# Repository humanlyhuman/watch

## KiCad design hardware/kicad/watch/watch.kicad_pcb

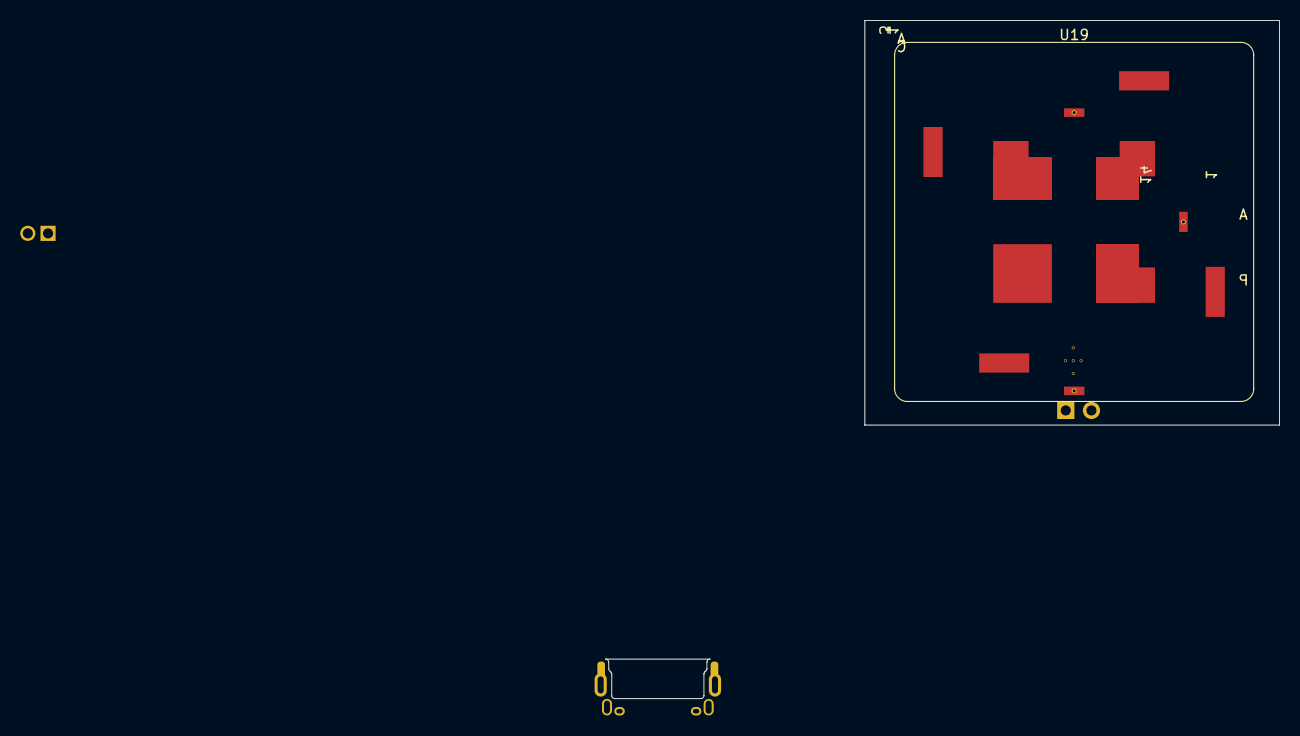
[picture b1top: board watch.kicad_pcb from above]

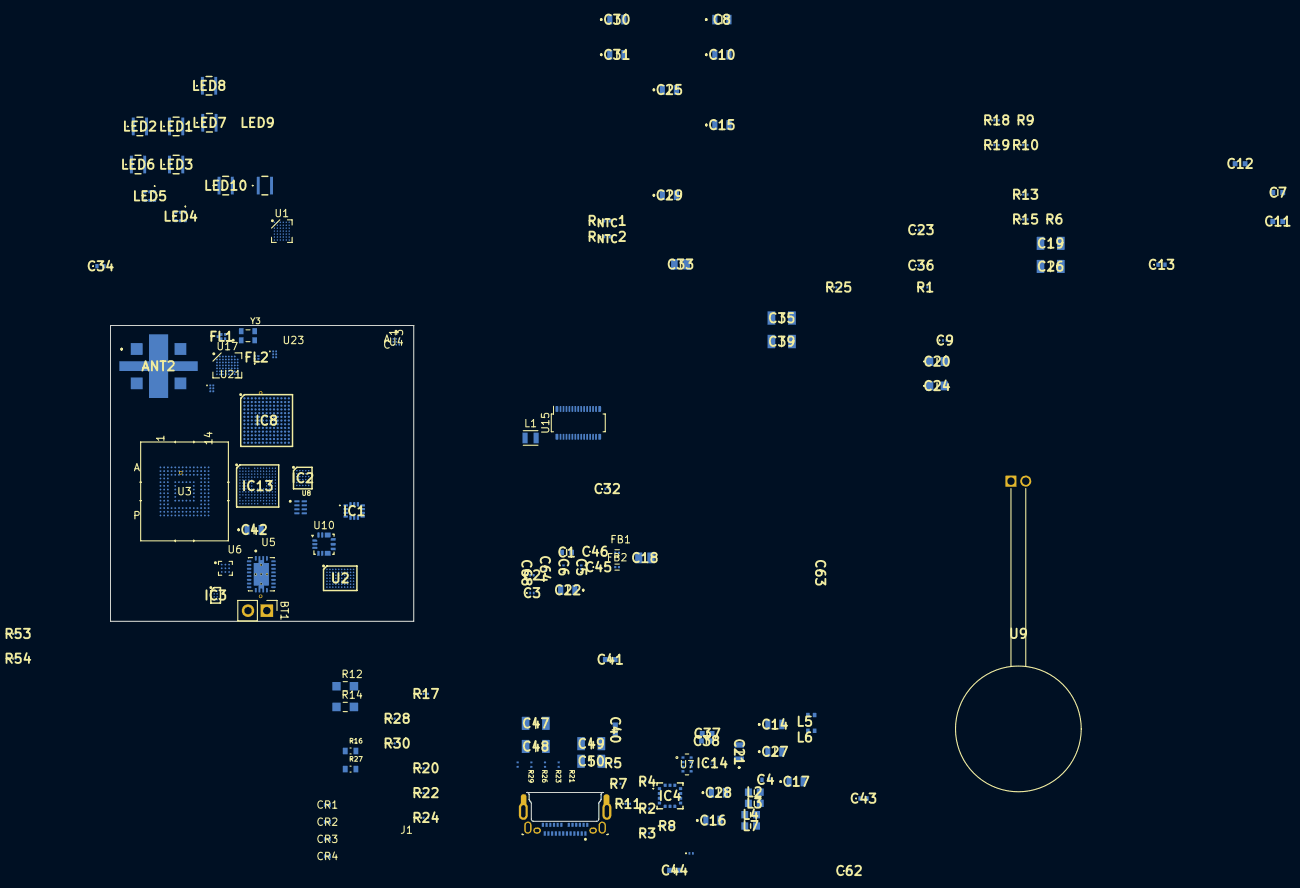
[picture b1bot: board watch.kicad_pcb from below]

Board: 8 copper layers, 139 parts (138 on the bottom side), 133 nets, no tracks yet.

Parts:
ANT2: HC125A
BT1: DTP793435-1S1P-1300mAh-3.85V; PinHeader_1x02_P2.54mm_Vertical
C1, C7, C11, C12, C44: 2.2uF; GRM18x
C2, C3, C5, C6, C9, C32, C36, C45, C46, C62, C63, C64, C68: 100nF; GRM033D70J224ME01D
C4, C13, C34, C43: 1uF; GRM155R61H334ME01D
C8, C14, C16, C17, C21, C22, C27, C28: 22uF; GRM21BR60J226ME39L
C10, C15, C25, C29, C30, C31, C42: 10uF; GRM21BR60J226ME39L
C18: 22nF; CAPC2012X145N
C19, C26: 10nF; CAPC3216X95N
C20, C24: 100nF; GRMJN65C1H104JE01D
C23: 1nF; GRM033D70J224ME01D
C33: 22nF; CAPC2012X135N
C35, C39: 470nF; CAPC3216X180N
C37, C38, C40, C41: 4.7uF; GRM18x
C47, C48, C49, C50: 47nF; CAPC3216X95N
CR1, CR2, CR3, CR4: SP0402B-ULC-01ETG; SP0402_LTF
FB1, FB2: 0201_782219121; FB_Wurth_WE-CBA-0201
FL1: B39162B4300F210
FL2: B39122B7505L210
IC1: LSM6DSV80XTR; LSM6DSV16BXTR
IC2: ICE40UP5K-UWG30ITR; BGA30C40P5X6_211X254X60
IC3: BQ21088YBGR; BGA8C40P2X4_100X155X50
IC4: ICU-10201; ICU10201
IC8: AKD1500PFC040BA; BGA169C50P13X13_700X700X130
IC13: AP510BFA-CBR; BGA153C40P13X13_560X560X80
IC14: AS6223A-AWLT; AS6223AAWLT
J1: CX90MWD2G-24P; HIROSE_CX90MWD2G-24P
L1: 2.2uH; L_Wurth_WE-PMCI-201210
L2, L3, L4, L7: 1uH; INDC1608X80N
L5, L6: 8.2nH; WE-TCI_040286
LED1, LED2, LED3, LED6, LED7, LED8, LED9, LED10: SFH_2705; SFH2705
LED4, LED5: SFH_7014H; SFH7014H
R1: 4.99k; ERJU01__0201_
R2, R4: 4.7k; ERJU01__0201_
R3, R5, R20, R22, R24, R28: 5.1k; ERJU01__0201_
R6, R15: 10k; ERJU01__0201_
R7, R11: 2k; ERJU01__0201_
R8: 10k; ERJS02_U02__0402_
R9, R10: 33; ERJU01__0201_
R12, R14: 1M; RES_ERJ-PC6B1004V
R13: 196; ERJU01__0201_
R16, R27: 51K; RES_ERA3AEB513V
R17, R30: 47k; ERJU01__0201_
R18, R19: 1M; ERJU01__0201_
R21, R23, R26, R29: 100k; RES_ERJU01F1003C
R25: 1.5k; ERJU01__0201_
R53, R54: 100; ERJU01__0201_
R_{NTC}1, R_{NTC}2: 10k; ERTJ0EA101H
U1: AS7058; BGA-42_6x7_2.545x2.815mm
U2: MAX77714EWC_T; BGA70C40P10X7_412X317X69
U3: KLMCG4JETD-B041; KLMBG2JETD-B041_SAM-M
U4: BMM350; BGA9_BMM350_BOS
U5: BQ51013CQWRHLRQ1; IC_BQ51013CQWRHLRQ1
U6: BQ27427YZFR
U7: TCS35303-2M; SMD8_TCS3530_OSM
U8: RV-3028-C8-32.768KHZ-1PPM-TA-QC
U9: 760308101214
U10: MAX77827AEFD; Maxim_FC2QFN-14_2.5x2.5mm_P0.5mm
U15: ET020AM03-HT; OCN_OK-01GM030-04_2x15_P0.4mm_Vertical
U17: CXD5610GF; BGA-56_8x7_3.66x3.147mm
U19: HP5354.A; TAOGLAS_HP5354.A
U21, U23: BGA524N6; INF-PG-TSNP-6-2-V
Y3: ECS-TXO-20CSMV4-260-AN-TR; OSC_ECS-TXO-20CSMV4-260-AN-TR

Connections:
32.768 kHz: IC4.9 (LFCLK), U2.B1 (XIN), U8.1 (CLKOUT), U17.G4 (RTC_CLK_IN)
+0V8: C45.1, FB1.2, IC8.D1 (VDD08_1), IC8.D2 (VDD08_2), IC8.D3 (VDD08_3), IC8.D4 (VDD08_4), IC8.D5 (VDD08_5), IC8.D6 (VDD08_6), IC8.D7 (VDD08_7), IC8.D8 (VDD08_8), IC8.F1 (VDD08_9), IC8.F2 (VDD08_10), IC8.F3 (VDD08_11), IC8.F4 (VDD08_12), IC8.F5 (VDD08_13), IC8.F6 (VDD08_14), IC8.F7 (VDD08_15), IC8.H1 (VDD08_17), IC8.H2 (VDD08_18), IC8.H3 (VDD08_19), IC8.H4 (VDD08_20), IC8.H5 (VDD08_21), IC8.H6 (VDD08_22), IC8.H7 (VDD08_23), IC8.H8 (VDD08_24), U2.B8 (OUT_LDO1), U17.C5 (VDD_CORE)
+0V65: U2.B6 (OUT_LDO0), U17.A4 (VDDA_ANA), U17.B2 (VDDA_LNA), U17.C2 (VDDA_LO0), U17.D3 (VDDA_LO1)
+1V2: U2.F6 (FB_SD2), U17.E1 (VDDA_LDO_C), U17.E2 (VDDA_LDO_M), U17.E3 (VDDA_LDO_A)
+1V8: C2.1, C3.1, C4.1, C5.2, C6.2, C34.2, C42.1, C43.1, C44.1, C46.1, FB2.2, IC1.5 (VDDIO), IC1.8 (VDD), IC4.12 (VDD), IC4.13 (AVDD), IC4.14 (VDDIO), IC8.D9 (VDE18_1), IC8.E9 (VDE18_2), IC8.F9 (VDE18_3), IC8.G9 (VDE18_4), IC8.H9 (VDE18_5), IC8.J8 (VDE18_6), IC8.J9 (VDE18_7), IC8.J10 (VDE18_8), IC8.K3 (VDE18_9), IC8.K4 (VDE18_10), IC8.K5 (VDE18_11), IC8.K6 (VDE18_12), IC8.K7 (VDE18_13), IC13.B1 (VDDP), IC13.B13 (VDDH), IC13.C5 (VDDA), IC13.C13 (VDDH2), IC13.D1 (VDDH1), IC13.E13 (BLE_VIO), IC13.F1 (BLE_VCC), IC13.G1 (BLE_VBAT2), IC13.G10 (VDDH4), IC13.H12 (VDDH3), IC13.N11 (VDD18), IC14.A1 (VDD), R2.2, R4.2, R7.2, R8.2, R11.2, U1.E5 (IOVDD), U1.E6 (DVDD), U1.F1 (AVDD2), U1.G4 (AVDD1), U2.C8 (FB_SD1), U2.F2 (INI2C), U3.C2 (VDDI), U3.C6 (VDD), U3.M4 (VDD), U3.N4 (VDD), U3.P3 (VDD), U3.P5 (VDD), U4.B3 (VDDIO), U4.C1 (VDD), U7.3 (VDD), U7.5 (VBUS), U8.7 (VDD), U17.B8 (VDD_IO_NV), U17.D1 (VDDA_IO), U17.F1 (VDDA_LDO_BCKP), U17.F5 (VDD_IO0), U17.F8 (VDD_IO_NV), U17.G8 (VDD_IO0), U21.2 (VCC), U23.2 (VCC), Y3.4 (VDD)
+5V: C31.1, J1.A4 (VBUS_A), J1.A9 (VBUS_A), J1.B4 (VBUS_B), J1.B9 (VBUS_B), U10.11 (OUT), U10.13 (OUTS)
+VSYS: BT1.1 (+), C8.1, C11.1, C12.2, C13.1, C30.1, C36.2, IC3.B2 (SYS), IC3.C2 (BAT), R15.2, R18.2, R19.2, U2.A3 (IN_LDO4_6), U2.A5 (IN_LDO2), U2.A7 (IN_LDO7_8), U2.A9 (IN_SD1), U2.A10 (IN_SD1), U2.B3 (IN_LDO3_5), U2.B7 (IN_LDO0_1), U2.D9 (IN_SD0), U2.D10 (IN_SD0), U2.E9 (IN_SD0), U2.F1 (BBATT), U2.F7 (MBATT), U2.G2 (IN_SD3), U2.G7 (IN_SD2), U6.B2 (VSS), U6.C1 (VSS), U6.C2 (SRX), U6.C3 (BAT), U10.6 (IN)
/Connectivity/20MHz: U17.A3 (CLK_IN), Y3.3 (OUTPUT)
/Connectivity/ANT2_2: ANT2.2, L6.1
/Connectivity/HP5354_11: L5.1, U19.11 (L5)
/Connectivity/L1: FL1.1 (INPUT), U21.3 (AO)
/Connectivity/L5: FL2.1 (INPUT), U23.3 (AO)
/Connectivity/RF1: FL2.3 (OUTPUT), U17.B1 (RF1_IN)
/Health/BIOZ1: C47.1, R21.1, U1.D2 (BIOZ1)
/Health/BIOZ2: C48.1, R23.1, U1.E2 (BIOZ4)
/Health/BIOZ3: C49.1, R26.1, U1.D1 (BIOZ2)
/Health/BIOZ4: C50.1, R29.1, U1.E1 (BIOZ4)
/Health/BLUE1: LED4.6 (CATHODE_BLUE_EMITTER_(460_NM)), U1.A6 (LED1)
/Health/BLUE2: LED5.6 (CATHODE_BLUE_EMITTER_(460_NM)), U1.A5 (LED3)
/Health/ECG_INN: R12.2, R16.1, U1.G6 (ECG_INN)
/Health/ECG_INP: R14.2, R27.1, U1.F6 (ECG_INP)
/Health/GREEN1: LED4.3 (CATHODE_GREEN_EMITTER_(530_NM)), U1.B1 (LED6)
/Health/GREEN2: LED5.3 (CATHODE_GREEN_EMITTER_(530_NM)), U1.A3 (LED9)
/Health/IR1: LED4.1 (CATHODE_IR_EMITTER_(940_NM)), U1.A1 (LED5)
/Health/IR2: LED5.1 (CATHODE_IR_EMITTER_(940_NM)), U1.A2 (LED7)
/Health/PDREF: LED1.1 (K), LED2.1 (K), LED3.1 (K), LED6.1 (K), LED7.1 (K), LED8.1 (K), LED9.1 (K), LED10.1 (K), U1.G1 (PDREF)
/Health/RED1: LED4.4 (CATHODE_RED_EMITTER_(655_NM)), U1.B6 (LED2)
/Health/RED2: LED5.4 (CATHODE_RED_EMITTER_(655_NM)), U1.A4 (LED4)
/MCU/DN: IC13.M10 (USB0PN), J1.A7 (D1-), J1.B6 (D2+)
/MCU/DP: IC13.M9 (USB0PP), J1.A6 (D1+), J1.B7 (D2-)
/MCU/MIPI_CLKN: IC13.L13 (MIPI_CLKN), U15.27 (CLKN)
/MCU/MIPI_CLKP: IC13.K13 (MIPI_CLKP), U15.26 (CLKP)
/MCU/MIPI_D0N: IC13.M13 (MIPI_D0N), U15.30 (D0N)
/MCU/MIPI_D0P: IC13.N13 (MIPI_D0P), U15.29 (D0P)
/MCU/MIPI_TE: IC13.C6 (GPIO10), U15.21 (TE)
/MCU/VDDAPLL18: FB2.1, IC8.G10 (VDDAPLL18)
/MCU/VDDC: C37.1, IC13.A3 (VDDC)
/MCU/VDDC_LV: C38.1, IC13.B3 (VDDC_LV)
/MCU/VDDF: C41.1, IC13.C2 (VDDF)
/MCU/VDDPLL08: FB1.1, IC8.H10 (VDDPLL08)
/MCU/VDDS: C40.1, IC13.C1 (VDDS)
/Motion/BMM350_C2: C1.1, U4.C2 (CRST)
/Power/AC1: C23.1, U5.2 (AC1), U9.2
/Power/AC2: C20.1, C23.2, U5.19 (AC2)
/Power/BIAS: C29.1, U10.5 (BIAS)
/Power/BOOT1: C39.1, U5.3 (BOOT1)
/Power/BOOT2: C35.1, U5.17 (BOOT2)
/Power/CLAMP1: C26.1, U5.5 (CLAMP1)
/Power/CLAMP2: C19.1, U5.16 (CLAMP2)
/Power/COMM1: C33.1, U5.6 (COMM1)
/Power/COMM2: C18.1, U5.15 (COMM2)
/Power/LX_SD0: L4.1, U2.E10 (LX_SD0), U2.F9 (LX_SD0), U2.F10 (LX_SD0)
/Power/LX_SD1: L2.1, U2.B9 (LX_SD1), U2.B10 (LX_SD1)
/Power/LX_SD2: L3.1, U2.G6 (LX_SD2)
/Power/LX_SD3: L7.1, U2.G3 (LX_SD3)
/Power/SEL: R1.1, U10.1 (SEL)
/Power/V_WIRELESS: C7.1, C24.1, C25.1, IC3.A2 (IN), R25.2, U5.4 (OUT)
AS7058_INT: IC13.J11 (GPIO70), IC13.L4 (GPIO0), U1.D5 (INT)
BGA524N6_PON: IC13.C10 (GPIO51), U21.6 (PON), U23.6 (PON)
BMM350_INT: IC13.M3 (GPIO20), U4.A1 (INT)
BQ21088YBGR_INT: IC3.A1 (~INT), IC13.L11 (GPIO83)
CXD5610GF_RESETX: IC13.C4 (GPIO19), U17.D4 (RESET_X)
DAT0: IC13.H10 (GPIO84), U3.A3 (DAT0)
DAT1: IC13.J10 (GPIO85), U3.A4 (DAT1)
DAT2: IC13.K10 (GPIO86), U3.A5 (DAT2)
DAT3: IC13.L9 (GPIO87), U3.B2 (DAT3)
DAT4: IC13.H7 (GPIO156), U3.B3 (DAT4)
DAT5: IC13.J7 (GPIO157), U3.B4 (DAT5)
DAT6: IC13.K7 (GPIO158), U3.B5 (DAT6)
DAT7: IC13.L8 (GPIO159), U3.B6 (DAT7)
GND: C1.2, C2.2, C3.2, C4.2, C5.1, C6.1, C11.2, C14.2, C16.2, C17.2, C21.2, C22.2, C27.2, C28.2, C29.2, C30.2, C31.2, C32.2, C34.1, C36.1, C37.2, C38.2, C40.2, C41.2, C42.2, C43.2, C44.2, C45.2, C46.2, C62.1, C63.1, C64.2, C68.1, CR1.2, CR2.2, CR3.2, CR4.2, FL1.2 (TO_BE_GROUNDED_1), FL1.3 (TO_BE_GROUNDED_2), FL1.5 (TO_BE_GROUNDED_3), FL2.2 (GROUND_1), FL2.4 (GROUND_2), IC1.2 (SDX), IC1.3 (SCX), IC1.6 (GND_1), IC1.7 (GND_2), IC2.B4 (GND_1), IC2.E2 (GND_2), IC4.1 (GND_1), IC4.8 (GND_2), IC4.11 (GND_3), IC8.A1 (GND_1), IC8.A2 (VPH_33), IC8.A3 (VP08), IC8.A4 (VPTX108), IC8.A5 (GND_2), IC8.A11 (GND_3), IC8.B5 (GND_7), IC8.B11 (GND_8), IC8.C1 (GND_9), IC8.C2 (GND_10), IC8.C3 (GND_11), IC8.C4 (GND_12), IC8.C5 (GND_13), IC8.C6 (GND_14), IC8.C7 (GND_15), IC8.C8 (GND_16), IC8.C9 (GND_17), IC8.C10 (GND_18), IC8.C12 (GND_19), IC8.D10 (GND_20), IC8.E1 (GND_21), IC8.E2 (GND_22), IC8.E3 (GND_23), IC8.E4 (GND_24), IC8.E5 (GND_25), IC8.E6 (GND_26), IC8.E7 (GND_27), IC8.E8 (GND_28), IC8.E10 (GND_29), IC8.E12 (GND_30), IC8.F10 (GND_31), IC8.G1 (GND_32), IC8.G2 (GND_33), IC8.G3 (GND_34), IC8.G4 (GND_35), IC8.G5 (GND_36), IC8.G6 (GND_37), IC8.G7 (GND_38), IC8.G8 (GND_39), IC8.G11 (GND_40), IC8.G13 (GND_41), IC8.J1 (GND_43), IC8.J2 (GND_44), IC8.J3 (GND_45), IC8.J4 (GND_46), IC8.J5 (GND_47), IC8.J6 (GND_48), IC8.J7 (GND_49), IC8.J11 (GND_50), IC8.J12 (GND_51), IC8.K10 (GND_52), IC8.L3 (GND_54), IC8.L4 (GND_55), IC8.L5 (GND_56), IC8.L6 (GND_57), IC8.L7 (GND_58), IC8.L8 (GND_59), IC8.L9 (GND_60), IC8.M1 (GND_61), IC8.M8 (GND_62), IC8.M12 (GND_63), IC8.N1 (GND_64), IC8.N10 (GND_65), IC8.N13 (GND_66), IC13.A6 (BLE_VSS_DCDC), IC13.B2 (VSSP), IC13.B4 (VSSA), IC13.C12 (VSSAUDA), IC13.E1 (BLE_VSS1), IC13.K11 (VSS), IC13.N10 (VSSAUSB), IC13.N12 (VSS18), IC14.A2 (GND), J1.A1 (GND_A), J1.A12 (GND_A), J1.B1 (GND_B), J1.B12 (GND_B), J1.SH1 (SHIELD), J1.SH2 (SHIELD), J1.SH3 (SHIELD), J1.SH4 (SHIELD), J1.SH5 (SHIELD), J1.SH6 (SHIELD), R1.2, R3.2, R5.2, R12.1, R14.1, R17.2, R30.2, R53.2, R54.2, U1.D6 (DGND), U1.F2 (AGND2), U1.F5 (ECG_REF), U1.G5 (AGND1), U2.C2 (XGND), U2.C3 (AGND), U2.C4 (DGND), U2.F4 (AV_SD), U3.A6 (VSS), U3.C4 (VSS), U3.E7 (VSS), U3.G5 (VSS), U3.H10 (VSS), U3.J5 (VSS), U3.K8 (VSS), U3.N2 (VSS), U3.N5 (VSS), U3.P4 (VSS), U3.P6 (VSS), U4.B1 (GND), U4.B2 (ADSEL), U4.C3 (BYPASS), U7.4 (VSS), U8.5 (VSS), U10.4 (PGND), U10.9 (PGND), U15.1 (GND), U15.7 (GND), U15.12 (GND), U15.17 (DCX), U15.18 (WRX_SCL), U15.22 (GND), U15.25 (GND), U15.28 (GND), U17.A2 (VSSA_LNA), U17.A7 (VQPS), U17.B3 (VSSA_LO0), U17.B4 (VSSA_ANA), U17.C1 (VSSA_IO), U17.C3 (VSSA_LO1), U17.C4 (TEST), U17.C6 (P/SDA0), U17.F7 (VSS), U17.G1 (VSSA_IO), U17.G3 (VSS), U19.3 (GND), U19.4 (GND), U19.5 (GND), U19.6 (GND), U19.7 (GND), U19.8 (GND), U19.9 (GND), U19.10 (GND), U21.1 (GND@1), U21.4 (GND@2), U23.1 (GND@1), U23.4 (GND@2), Y3.1 (GROUND), Y3.2 (GROUND)
GNDPWR: BT1.2 (-), C7.2, C8.2, C9.1, C10.1, C13.2, C15.1, C18.2, C19.2, C24.2, C25.2, C26.2, C33.2, C35.2, C39.2, IC3.D2 (GND), R6.2, R9.1, R10.2, R13.2, R_{NTC}1.2, R_{NTC}2.2, U1.B2 (PGND2), U2.C9 (PG_SD1), U2.C10 (PG_SD1), U2.F8 (PG_SD0), U2.G4 (PG_SD2_3), U2.G5 (PG_SD2_3), U2.G8 (PG_SD0), U2.G9 (PG_SD0), U2.G10 (PG_SD0), U5.1 (PGND), U5.9 (AD), U5.12 (ILIM), U5.20 (PGND), U5.21 (EXP), U7.2 (PGND)
I2C_SCL: IC13.D5 (GPIO8), IC14.B2 (SCL), R4.1, U2.D1 (SCL)
I2C_SDA: IC13.B6 (GPIO9), IC14.B1 (SDA), R2.1, U2.E1 (SDA)
I3C_SCL: IC2.A1 (IOT_36B), IC3.B1 (SCL), R7.1, U4.A3 (SCK), U7.7 (SCL), U8.3 (SCL)
I3C_SDA: IC2.A2 (IOT_37A), IC3.C1 (SDA), R11.1, U4.A2 (SDA), U7.6 (SDA), U8.4 (SDA)
ICU-10201_INT1: IC4.6 (INT1), IC13.D2 (GPIO145)
ICU-10201_INT2: IC4.7 (INT2), IC13.D3 (GPIO147)
LSM6DSV80XTR_INT1: IC1.4 (INT1), IC13.L1 (GPIO28)
LSM6DSV80XTR_INT2: IC1.9 (INT2), IC13.L3 (GPIO32)
MAX77714_EN0: IC13.M5 (GPIO29), U2.C7 (EN0)
MAX77714_EN1: IC13.M6 (GPIO4), U2.C6 (EN1)
MAX77714_SHDN: IC13.B7 (GPIO12), U2.D8 (SHDN)
MAX77827_EN: IC13.M4 (GPIO2), U10.3 (EN)
unnamed: ANT2.3, R53.1, R54.1
unnamed: C14.1, C27.1, C28.1, L4.2
unnamed: C16.1, L7.2
unnamed: C17.1, L3.2
unnamed: C20.2, U9.1
unnamed: C21.1, C22.1, L2.2
unnamed: C47.2, R20.1, R21.2
unnamed: C48.2, R22.1, R23.2
unnamed: C49.2, R24.1, R26.2
unnamed: C50.2, R28.1, R29.2
unnamed: IC3.D1 (TS/MR), R6.1
unnamed: IC13.A1 (SIMOBUCK_SW), L1.1
unnamed: IC13.A2 (SIMOBUCK_SW_SEL), L1.2
unnamed: J1.A5 (CC1), R5.1
unnamed: J1.B5 (CC2), R3.1
unnamed: CR1.1, R16.2, R22.2
unnamed: CR3.1, R20.2
unnamed: CR4.1, R24.2, R27.2
unnamed: CR2.1, R28.2
unnamed: LED1.2 (A), U1.E4 (PD1)
unnamed: LED2.2 (A), U1.G3 (PD2)
unnamed: LED3.2 (A), U1.F4 (PD3)
unnamed: LED6.2 (A), U1.D4
unnamed: LED7.2 (A), U1.G2 (PD5)
unnamed: LED8.2 (A), U1.D3 (PD6)
unnamed: LED9.2 (A), U1.F3 (PD7)
unnamed: LED10.2 (A), U1.E3 (PD8)
unnamed: R9.2, R10.1
unnamed: R30.1, U1.B3 (EXTCLK)
unnamed: R17.1, U1.C3 (GPIO)
unnamed: R13.1, U5.14 (FOD)
unnamed: C9.2, C10.2, C15.2, U5.18 (RECT)
unnamed: R25.1, R_{NTC}2.1, U5.13 (TS/CTRL)
unnamed: R_{NTC}1.1, U6.B1 (BIN)
unnamed: R15.1, U6.A1 (GPOUT)
unnamed: R18.1, U6.A3 (SCL)
unnamed: R19.1, U6.A2 (SDA)
unnamed: C12.1, U6.B3 (VDD)
unnamed: ANT2.1, U19.1 (L1P1)
unnamed: ANT2.4, U19.2 (L1P2)
unnamed: L6.2, U21.5 (AI)
unnamed: L5.2, U23.5 (AI)
SDMMC_CLK: IC13.K9 (GPIO88), U3.M6 (CLK)
SDMMC_CMD: IC13.K8 (GPIO160), U3.M5 (CMD)
SPI_CS: IC1.12 (CS), IC4.5 (CS_B), IC13.H5 (GPIO16), R8.1, U1.B4 (CSXN), U17.B5 (P/CTS/CS)
SPI_MISO: IC1.1 (SDO/SA0), IC1.14 (SDA), IC4.4 (MISO), IC13.J6 (GPIO7), U1.C4 (MISO), U17.B6 (P/RTS/MISO)
SPI_MOSI: IC4.3 (MOSI), IC13.K6 (GPIO6), U1.C5 (SDA_MOSI), U17.A5 (TX/SDA/MOSI)
SPI_SCLK: IC1.13 (SCL), IC4.2 (SCLK), IC13.L6 (GPIO5), U1.C6 (SCL), U17.A6 (RX/SCL/SCLK)
VDD: C32.1, C62.2, C63.2, C64.1, C68.2, IC13.N9 (VDDUSB33), LED4.2 (ANODE_BLUE/_GREEN/_RED/_IR_EMITTER_1), LED4.5 (ANODE_BLUE/_GREEN/_RED/_IR_EMITTER_2), LED5.2 (ANODE_BLUE/_GREEN/_RED/_IR_EMITTER_1), LED5.5 (ANODE_BLUE/_GREEN/_RED/_IR_EMITTER_2), U1.C2 (VCSELS), U2.E8 (FB_SD0), U3.E6 (VDDF), U3.F5 (VDDF), U3.J10 (VDDF), U3.K9 (VDDF), U15.6 (TP_3.3V), U15.8 (IOVCC), U15.9 (VCI), U15.10 (VBAT), U15.11 (VCI_EN)
